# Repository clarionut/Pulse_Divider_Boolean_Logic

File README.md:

# Pulse Divider and Boolean Logic

A synthesizer module based on the [original CGS36 circuit](https://sdiy.info/wiki/CGS_pulse_divider_and_Boolean_logic).

I was particularly concerned about high current consumption as the original outputs put 15V across a potential divider with a total resistance of 2.8k.
Even at Eurorack levels of 12V that's over 4mA per 'on' output, not counting the LEDs. Instead I powered the outputs from a dedicated 78L09 9V supply
(I like strong gate/trigger signals) and removed the resistor chain to ground.

The pulse divider now has a /1 output, which is a buffered copy of the incoming clock at the same voltage level as the divided outputs.

There are significant changes to the logic gates too
- the AND and OR gates have the same modification to their outputs as the pulse divider stages
- the original XOR gate can only compare signals of approximately the same voltage. This version has a voltage conditioner on its inputs (using op-amp comparators), allowing a wider range of input signals to be processed.
- the XOR comparator / output stage is an LM324 running on +9V
- the dedicated XNOR circuitry has been removed
- the NOT gates are replaced by 3 op-amp inverters using the remaining stages of the LM324. These are normalled to the AND, OR and XOR outputs providing NAND, NOR and XNOR functions by default, but can be used to invert any other logic signal for maximum flexibility

For reasons of economy I built the pulse divider and Boolean logic circuits on two separate PCBs. The logic board is daisy-chained from the divider board for its power supply, and also uses two stages of the TL084 as its input voltage conditioner. To build this board as a stand-alone unit will require a redesign with power input circuitry and a TL082 as the voltage conditioner.

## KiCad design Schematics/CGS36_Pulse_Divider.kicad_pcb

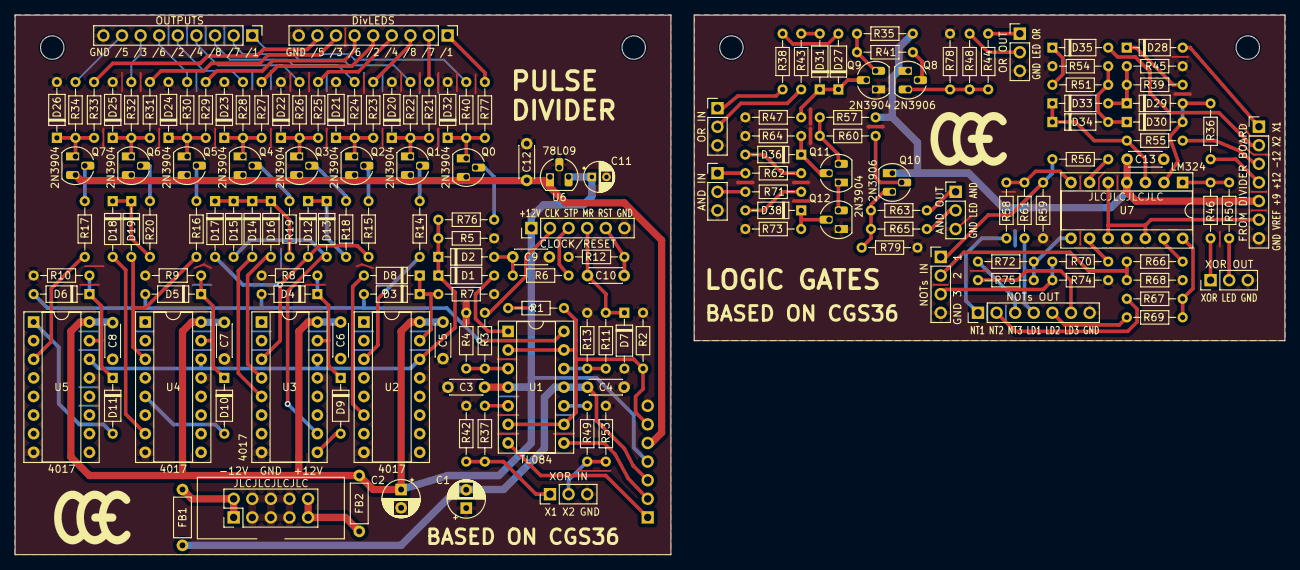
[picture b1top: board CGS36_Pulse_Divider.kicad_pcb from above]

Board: 2 copper layers, 173.4 x 73.7 mm, 164 parts (1 on the bottom side), 127 nets.

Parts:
C1, C2: 10u; CP_Radial_D5.0mm_P2.50mm
C3, C4, C5, C6, C7, C8, C9, C12, C13: 100n; C_Disc_D4.3mm_W1.9mm_P5.00mm
C10: 10n; C_Disc_D4.3mm_W1.9mm_P5.00mm
C11: 1u; CP_Radial_D4.0mm_P2.00mm
D1, D2, D3, D4, D5, D6, D7, D8, D9, D10, D11, D12, D13, D14, D15, D16, D17, D18, D19, D20, D21, D22, D23, D24, D25, D26, D27, D28, D29, D30, D31, D32, D33, D34, D35, D36, D38: 1N914; D_DO-35_SOD27_P7.62mm_Horizontal
FB1, FB2: FB; L_Axial_L5.3mm_D2.2mm_P7.62mm_Horizontal_Vishay_IM-1
J1: POWER; Power_2x05
J2: CLK/RST; PinHeader_1x06_P2.54mm_Vertical
J3: XOR_IN; PinHeader_1x03_P2.54mm_Vertical
J4: TO_LOGIC; PinHeader_1x07_P2.54mm_Vertical
J5: DivLEDS; PinHeader_1x09_P2.54mm_Vertical
J6: DivOUT; PinHeader_1x09_P2.54mm_Vertical
J7: OR_IN; PinHeader_1x03_P2.54mm_Vertical
J8: OR_OUT; PinHeader_1x03_P2.54mm_Vertical
J9: FROM_DIVIDER; PinHeader_1x07_P2.54mm_Vertical
J10: XOR_OUT; PinHeader_1x03_P2.54mm_Vertical
J11: AND_OUT; PinHeader_1x03_P2.54mm_Vertical
J12: NOT_IN; PinHeader_1x04_P2.54mm_Vertical
J13: AND_IN; PinHeader_1x03_P2.54mm_Vertical
J14: NOT_OUT; PinHeader_1x07_P2.54mm_Vertical
Q0, Q1, Q2, Q3, Q4, Q5, Q6, Q7, Q9, Q11, Q12: 2N3904; TO-92_HandSolder
Q8, Q10: 2N3906; TO-92_HandSolder
R1, R4, R5, R7, R8, R9, R10, R12, R13, R35, R37, R38, R42, R43, R45, R49, R53, R54, R56, R57, R59, R62, R66, R68, R70, R71, R74, R78, R79: 100k; R_Axial_DIN0204_L3.6mm_D1.6mm_P7.62mm_Horizontal
R2, R61, R69, R75: 15k; R_Axial_DIN0204_L3.6mm_D1.6mm_P7.62mm_Horizontal
R3, R6, R11: 10k; R_Axial_DIN0204_L3.6mm_D1.6mm_P7.62mm_Horizontal
R14, R15, R16, R17, R18, R19, R20, R36, R47, R55, R64, R73, R76: 200k; R_Axial_DIN0204_L3.6mm_D1.6mm_P7.62mm_Horizontal
R21, R23, R25, R27, R29, R31, R33, R77: 33k; R_Axial_DIN0204_L3.6mm_D1.6mm_P7.62mm_Horizontal
R22, R24, R26, R28, R30, R32, R34, R40, R44, R63: 2k2; R_Axial_DIN0204_L3.6mm_D1.6mm_P7.62mm_Horizontal
R39, R51: 27k; R_Axial_DIN0204_L3.6mm_D1.6mm_P7.62mm_Horizontal
R41, R48, R50, R60, R65: 47k; R_Axial_DIN0204_L3.6mm_D1.6mm_P7.62mm_Horizontal
R46, R58, R67, R72: 1k; R_Axial_DIN0204_L3.6mm_D1.6mm_P7.62mm_Horizontal
U1: TL084; DIP-14_W7.62mm_Socket
U2, U3, U4, U5: 4017; DIP-16_W7.62mm_Socket
U6: L78L09_TO92; TO-92_HandSolder
U7: LM324; DIP-14_W7.62mm_Socket

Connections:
+9V: C12.1, J4.5, Q0.3 (C), Q1.3 (C), Q2.3 (C), Q3.3 (C), Q4.3 (C), Q5.3 (C), Q6.3 (C), Q7.3 (C), U6.1 (VO)
+9VA: C13.1, J9.5, Q8.1 (E), Q10.1 (E), R35.2, R57.2, U7.4 (V+)
+12V: C2.1, C3.1, C5.1, C6.1, C7.1, C8.1, C11.1, FB2.1, J2.1, J4.4, R1.2, U1.4 (V+), U2.16 (VDD), U3.16 (VDD), U4.16 (VDD), U5.16 (VDD), U6.3 (VI)
+12VA: J9.4, R36.2
-12V: C1.2, C4.1, FB1.1, J4.3, U1.11 (V-)
-12VA: J9.3, R55.1
/CLK: J2.2, R3.1
/L1: J5.1, R77.1
/L2: J5.5, R27.1
/L3: J5.7, R31.1
/L4: J5.4, R25.1
/L5: J5.8, R33.1
/L6: J5.6, R29.1
/L7: J5.2, R21.1
/L8: J5.3, R23.1
/Logic Gates/AND: J11.1, R63.1
/Logic Gates/AND1: J13.1, R62.2
/Logic Gates/AND2: J13.2, R71.2
/Logic Gates/ANDLED: J11.2, R65.1
/Logic Gates/NIN1: J12.1, R56.2, R59.2
/Logic Gates/NIN2: J12.2, R66.2, R68.2
/Logic Gates/NIN3: J12.3, R70.2, R74.2
/Logic Gates/NOT1: J14.1, R58.1
/Logic Gates/NOT1LED: J14.4, R61.1
/Logic Gates/NOT2: J14.2, R67.1
/Logic Gates/NOT2LED: J14.5, R69.1
/Logic Gates/NOT3: J14.3, R72.1
/Logic Gates/NOT3LED: J14.6, R75.1
/Logic Gates/OR: J8.1, R44.1
/Logic Gates/OR1: J7.1, R38.2
/Logic Gates/OR2: J7.2, R43.2
/Logic Gates/ORLED: J8.2, R48.1
/Logic Gates/X1A: D28.2 (A), J9.1
/Logic Gates/X2A: D35.2 (A), J9.2
/Logic Gates/XOR: J10.1, R46.1
/Logic Gates/XORLED: J10.2, R50.1
/MAN_RST: C10.2, D7.1 (K), J2.4, R11.1
/MAN_STP: J2.3, R6.1
/O1: J6.1, R40.1
/O2: J6.5, R28.1
/O3: J6.7, R32.1
/O4: J6.4, R26.1
/O5: J6.8, R34.1
/O6: J6.6, R30.1
/O7: J6.2, R22.1
/O8: J6.3, R24.1
/RESET: C10.1, J2.5, R12.2
/X1: J4.1, U1.7
/X2: J4.2, U1.8
/XOR1: J3.1, R37.2, R42.2
/XOR2: J3.2, R49.2, R53.2
GND: C1.1, C2.2, C3.2, C4.2, C5.2, C6.2, C7.2, C8.2, C9.2, C11.2, C12.2, D7.2 (A), D20.2 (A), D21.2 (A), D22.2 (A), D23.2 (A), D24.2 (A), D25.2 (A), D26.2 (A), D32.2 (A), J1.3, J1.4, J1.5, J1.6, J1.7, J1.8, J2.6, J3.3, J4.7, J5.9, J6.9, R2.1, R4.1, R5.1, R7.1, R8.1, R9.1, R10.1, R12.1, R13.1, R42.1, R53.1, U2.8 (VSS), U2.13 (CKEN), U3.8 (VSS), U3.13 (CKEN), U4.8 (VSS), U4.13 (CKEN), U5.8 (VSS), U5.13 (CKEN), U6.2 (GND)
GNDA: C13.2, J7.3, J8.3, J9.7, J10.3, J11.3, J12.4, J13.3, J14.7, Q9.1 (E), Q12.1 (E), R45.1, R47.1, R54.1, R59.1, R64.1, R68.1, R73.1, R74.1, R78.1, R79.1, U7.11 (V-)
unnamed: D1.2 (A), U1.1
unnamed: D1.1 (K), D2.1 (K), R5.2, R76.2, U2.14 (CLK), U3.14 (CLK), U4.14 (CLK), U5.14 (CLK)
unnamed: C9.1, D2.2 (A), R6.2
unnamed: D3.2 (A), D4.2 (A), D5.2 (A), D6.2 (A), U1.14
unnamed: D3.1 (K), D8.1 (K), R7.2, U2.15 (Reset)
unnamed: D4.1 (K), D9.1 (K), R8.2, U3.15 (Reset)
unnamed: D8.2 (A), U2.6 (Q7)
unnamed: D9.2 (A), U3.9 (Q8)
unnamed: D10.2 (A), U4.5 (Q6)
unnamed: D5.1 (K), D10.1 (K), R9.2, U4.15 (Reset)
unnamed: D11.2 (A), U5.1 (Q5)
unnamed: D6.1 (K), D11.1 (K), R10.2, U5.15 (Reset)
unnamed: D12.2 (A), D17.2 (A), R15.2, U3.3 (Q0)
unnamed: D12.1 (K), D13.1 (K), R18.1
unnamed: D13.2 (A), D15.2 (A), U3.10 (Q4)
unnamed: D14.2 (A), U3.5 (Q6)
unnamed: D14.1 (K), D15.1 (K), D16.1 (K), D17.1 (K), R19.1
unnamed: D16.2 (A), U3.4 (Q2)
unnamed: D18.2 (A), U4.7 (Q3)
unnamed: D18.1 (K), D19.1 (K), R20.1
unnamed: D19.2 (A), R16.2, U4.3 (Q0)
unnamed: D20.1 (K), Q1.1 (E), R21.2, R22.2
unnamed: D21.1 (K), Q2.1 (E), R23.2, R24.2
unnamed: D22.1 (K), Q3.1 (E), R25.2, R26.2
unnamed: D23.1 (K), Q4.1 (E), R27.2, R28.2
unnamed: D24.1 (K), Q5.1 (E), R29.2, R30.2
unnamed: D25.1 (K), Q6.1 (E), R31.2, R32.2
unnamed: D26.1 (K), Q7.1 (E), R33.2, R34.2
unnamed: D27.2 (A), R38.1
unnamed: D27.1 (K), D31.1 (K), Q9.2 (B), R47.2
unnamed: D28.1 (K), R39.2
unnamed: D29.2 (A), D30.2 (A), R36.1, U7.2 (-)
unnamed: D29.1 (K), D33.2 (A), R39.1, R45.2
unnamed: D30.1 (K), D34.2 (A), R51.1, R54.2
unnamed: D31.2 (A), R43.1
unnamed: D32.1 (K), Q0.1 (E), R40.2, R77.2
unnamed: D33.1 (K), D34.1 (K), R55.2, U7.3 (+)
unnamed: D35.1 (K), R51.2
unnamed: D36.2 (A), R62.1
unnamed: D36.1 (K), Q11.2 (B), R64.2
unnamed: D38.2 (A), R71.1
unnamed: D38.1 (K), Q12.2 (B), R73.2
unnamed: FB1.2, J1.1, J1.2
unnamed: FB2.2, J1.9, J1.10
unnamed: Q0.2 (B), R76.1
unnamed: Q1.2 (B), R14.1
unnamed: Q2.2 (B), R15.1
unnamed: Q3.2 (B), R18.2
unnamed: Q4.2 (B), R19.2
unnamed: Q5.2 (B), R16.1
unnamed: Q6.2 (B), R20.2
unnamed: Q7.2 (B), R17.1
unnamed: Q8.2 (B), R41.1
unnamed: Q8.3 (C), R44.2, R48.2, R78.2
unnamed: Q9.3 (C), R35.1, R41.2
unnamed: Q10.2 (B), R60.1
unnamed: Q10.3 (C), R63.2, R65.2, R79.2
unnamed: Q11.3 (C), R57.1, R60.2
unnamed: Q11.1 (E), Q12.3 (C)
unnamed: R46.2, R50.2, U7.1
unnamed: R58.2, R61.2, U7.7
unnamed: R67.2, R69.2, U7.14
unnamed: R72.2, R75.2, U7.8
unnamed: R3.2, R4.2, U1.3 (+)
unnamed: R37.1, U1.5 (+)
unnamed: R49.1, U1.10 (+)
unnamed: R11.2, R13.2, U1.12 (+)
unnamed: R14.2, U2.3 (Q0)
unnamed: R17.2, U5.3 (Q0)
unnamed: R56.1, U7.6 (-)
unnamed: R70.1, U7.9 (-)
unnamed: R66.1, U7.13 (-)
VREF: J4.6, R1.1, R2.2, U1.2 (-), U1.6 (-), U1.9 (-), U1.13 (-)
VREFA: J9.6, U7.5 (+), U7.10 (+), U7.12 (+)

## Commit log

2024-07-04 Create temp
